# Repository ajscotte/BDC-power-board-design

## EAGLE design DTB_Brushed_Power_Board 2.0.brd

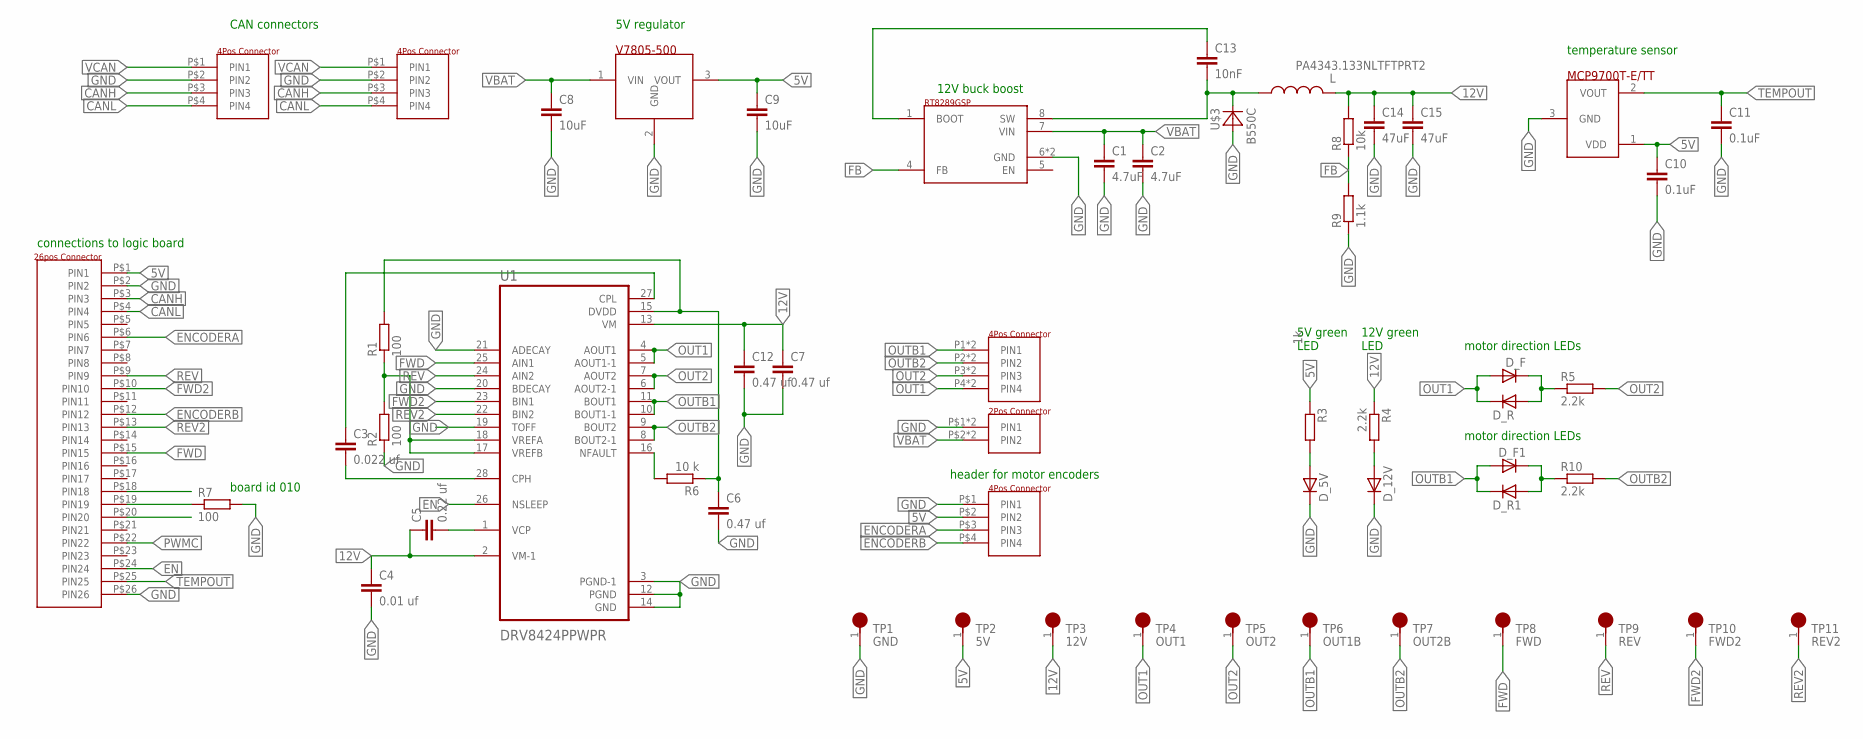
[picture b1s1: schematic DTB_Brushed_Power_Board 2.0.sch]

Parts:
C1, C2: 4.7uF; C1206
C3: 0.022 uf; C1206
C4: 0.01 uf; C1206
C5: 0.22 uf; C1206
C6, C7, C12: 0.47 uf; C1206
C8, C9: 10uF; C1206
C10, C11: 0.1uF; C0603
C13: 10nF; C1206
C14, C15: 47uF; C1206
D_5V, D_12V: LED0603; DO0603
D_F, D_F1: LED0603; DO0603
D_R, D_R1: LED0603; DO0603
L: PA4343.133NLTFTPRT2; INDM140128X650N
R1, R2, R7: 100; R0603
R3: 1k; R0603
R4, R5, R10: 2.2k; R0603
R6: 10 k; R0603
R8: 10k; R0603
R9: 1.1k; R0603
TP1: GND; HARWIN_S2751-46R
TP2: 5V; HARWIN_S2751-46R
TP3: 12V; HARWIN_S2751-46R
TP4: OUT1; HARWIN_S2751-46R
TP5: OUT2; HARWIN_S2751-46R
TP6: OUT1B; HARWIN_S2751-46R
TP7: OUT2B; HARWIN_S2751-46R
TP8: FWD; HARWIN_S2751-46R
TP9: REV; HARWIN_S2751-46R
TP10: FWD2; HARWIN_S2751-46R
TP11: REV2; HARWIN_S2751-46R
U1: DRV8424PPWPR; IC_TPS61196PWPRQ1
U$2: RT8289GSP; SO8
U$3: B550C; SMC
U$4: 2POS_CONNECTOR,1X2_45A_POWERPOLE; POWERPOLE_45A_1X2
U$6: 4POS_CONNECTORPOWERPOLE_1X4; POWERPOLE_45A_1X4
U$7, U$8: 4POS_CONNECTORMOLEX_MICROFIT3.0_RA_4PIN_2ROW; MOLEX_MICROFIT3.0_0430450400
U$9: V7805-500; SIP3
U$10: 26POS_CONNECTORN2526-6002-RB; N2526-6002-RB
U$11: MCP9700T-E/TT; SOT23
U$12: 4POS_CONNECTOR.1"HEADER; 4POS_HEADER_.1"

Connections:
5V: C9.1, C10.1, R3.1, TP2.1, U$9.3 (VOUT), U$10.P$1 (PIN1), U$11.1 (VDD), U$12.P$2 (PIN2)
12V: C4.1, C5.1, C7.1, C12.1, C14.1, C15.1, L.2, R4.1, R8.2, TP3.1, U1.2 (VM-1), U1.13 (VM)
BOOT: C13.1, U$2.1 (BOOT)
CANH: U$7.P$3 (PIN3), U$8.P$3 (PIN3), U$10.P$3 (PIN3)
CANL: U$7.P$4 (PIN4), U$8.P$4 (PIN4), U$10.P$4 (PIN4)
EN: U1.26 (NSLEEP), U$10.P$24 (PIN24)
ENCODERA: U$10.P$6 (PIN6), U$12.P$3 (PIN3)
ENCODERB: U$10.P$12 (PIN12), U$12.P$4 (PIN4)
FB: R8.1, R9.2, U$2.4 (FB)
FWD: TP8.1, U1.25 (AIN1), U$10.P$15 (PIN15)
FWD2: TP10.1, U1.23 (BIN1), U$10.P$10 (PIN10)
GND: C1.2, C2.2, C4.2, C6.2, C7.2, C8.2, C9.2, C10.2, C11.2, C12.2, C14.2, C15.2, D_5V.2 (C), D_12V.2 (C), R2.1, R7.2, R9.1, TP1.1, U1.3 (PGND-1), U1.12 (PGND), U1.14 (GND), U1.19 (TOFF), U1.20 (BDECAY), U1.21 (ADECAY), U$2.6 (GND), U$2.GND,EXPOSEDPAD (GND), U$3.A, U$4.P$1 (PIN1), U$4.P$5 (PIN1), U$7.P$2 (PIN2), U$8.P$2 (PIN2), U$9.2 (GND), U$10.P$2 (PIN2), U$10.P$26 (PIN26), U$11.3 (GND), U$12.P$1 (PIN1)
unnamed: R6.2, U1.16 (NFAULT)
unnamed: D_F.2 (C), D_R.1 (A), R5.1
unnamed: R7.1, U$10.P$19 (PIN19)
unnamed: C6.1, R1.2, R6.1, U1.15 (DVDD)
unnamed: D_5V.1 (A), R3.2
unnamed: D_12V.1 (A), R4.2
unnamed: C5.2, U1.1 (VCP)
unnamed: C13.2, L.1, U$2.8 (SW), U$3.C
unnamed: D_F1.2 (C), D_R1.1 (A), R10.1
unnamed: R1.1, R2.2, U1.17 (VREFB), U1.18 (VREFA)
unnamed: C3.2, U1.28 (CPH)
OUT1: D_F.1 (A), D_R.2 (C), TP4.1, U1.4 (AOUT1), U1.5 (AOUT1-1), U$6.P4 (PIN4), U$6.P4B (PIN4)
OUT2: R5.2, TP5.1, U1.6 (AOUT2-1), U1.7 (AOUT2), U$6.P3 (PIN3), U$6.P3B (PIN3)
OUTB1: D_F1.1 (A), D_R1.2 (C), TP6.1, U1.10 (BOUT1-1), U1.11 (BOUT1), U$6.P1 (PIN1), U$6.P1B (PIN1)
OUTB2: R10.2, TP7.1, U1.8 (BOUT2-1), U1.9 (BOUT2), U$6.P2 (PIN2), U$6.P2B (PIN2)
PWMC: U$10.P$22 (PIN22)
REV: TP9.1, U1.24 (AIN2), U$10.P$9 (PIN9)
REV2: TP11.1, U1.22 (BIN2), U$10.P$13 (PIN13)
TEMPOUT: C11.1, U$10.P$25 (PIN25), U$11.2 (VOUT)
VBAT: C1.1, C2.1, C8.1, U$2.7 (VIN), U$4.P$2 (PIN2), U$4.P$6 (PIN2), U$9.1 (VIN)
VBAT1: C3.1, U1.27 (CPL)
VCAN: U$7.P$1 (PIN1), U$8.P$1 (PIN1)

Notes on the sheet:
CAN connectors
5V regulator
connections to logic board
temperature sensor
board id 010
5V green LED
12V green LED
motor direction LEDs
header for motor encoders
12V buck boost

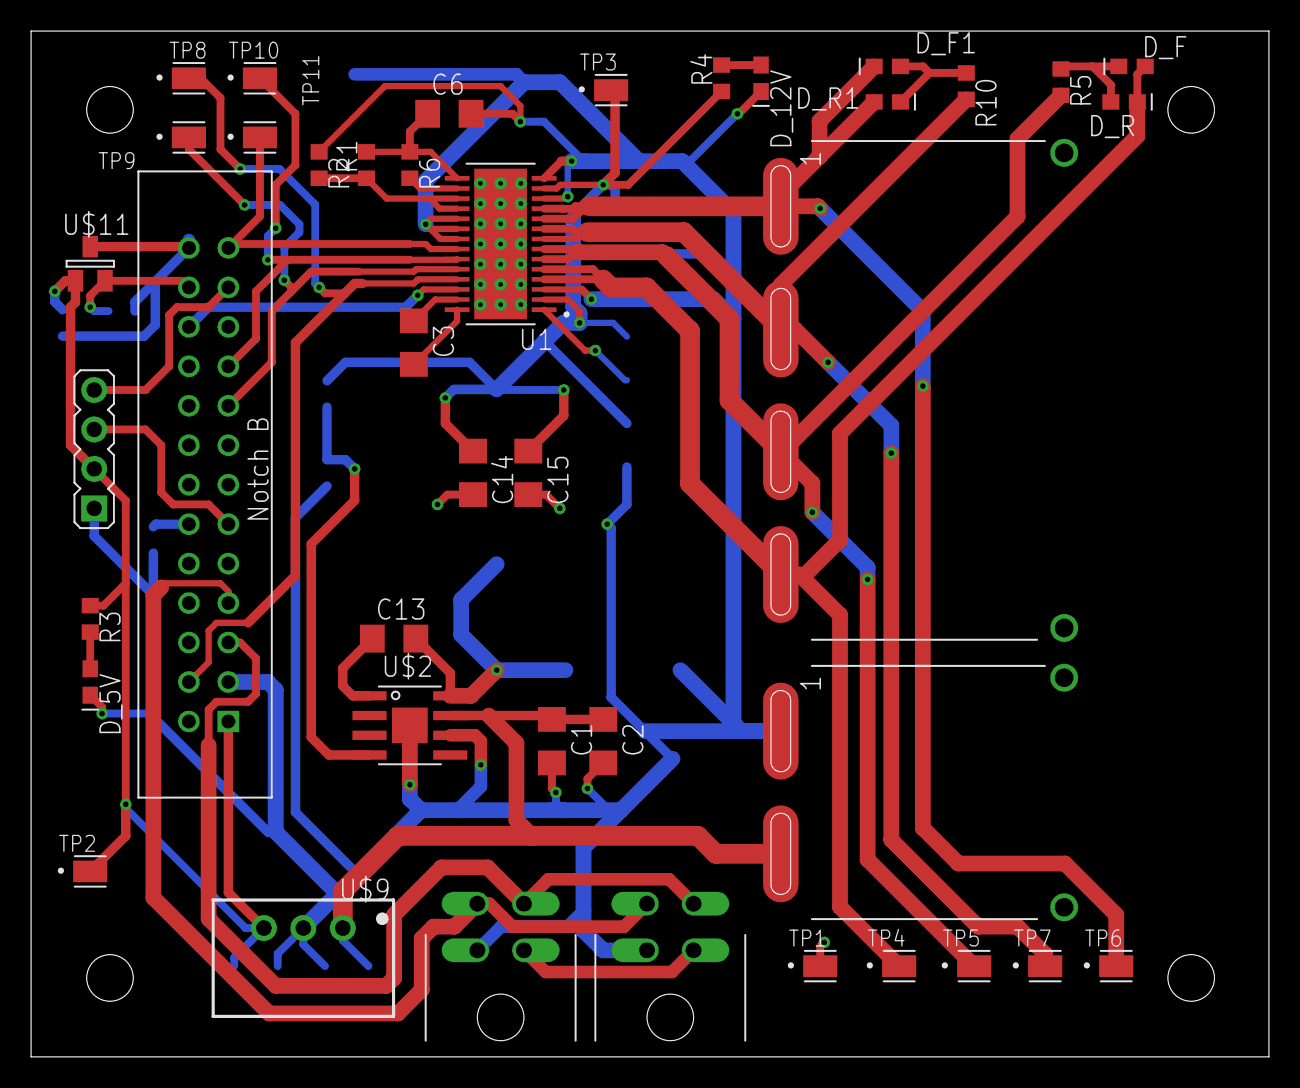
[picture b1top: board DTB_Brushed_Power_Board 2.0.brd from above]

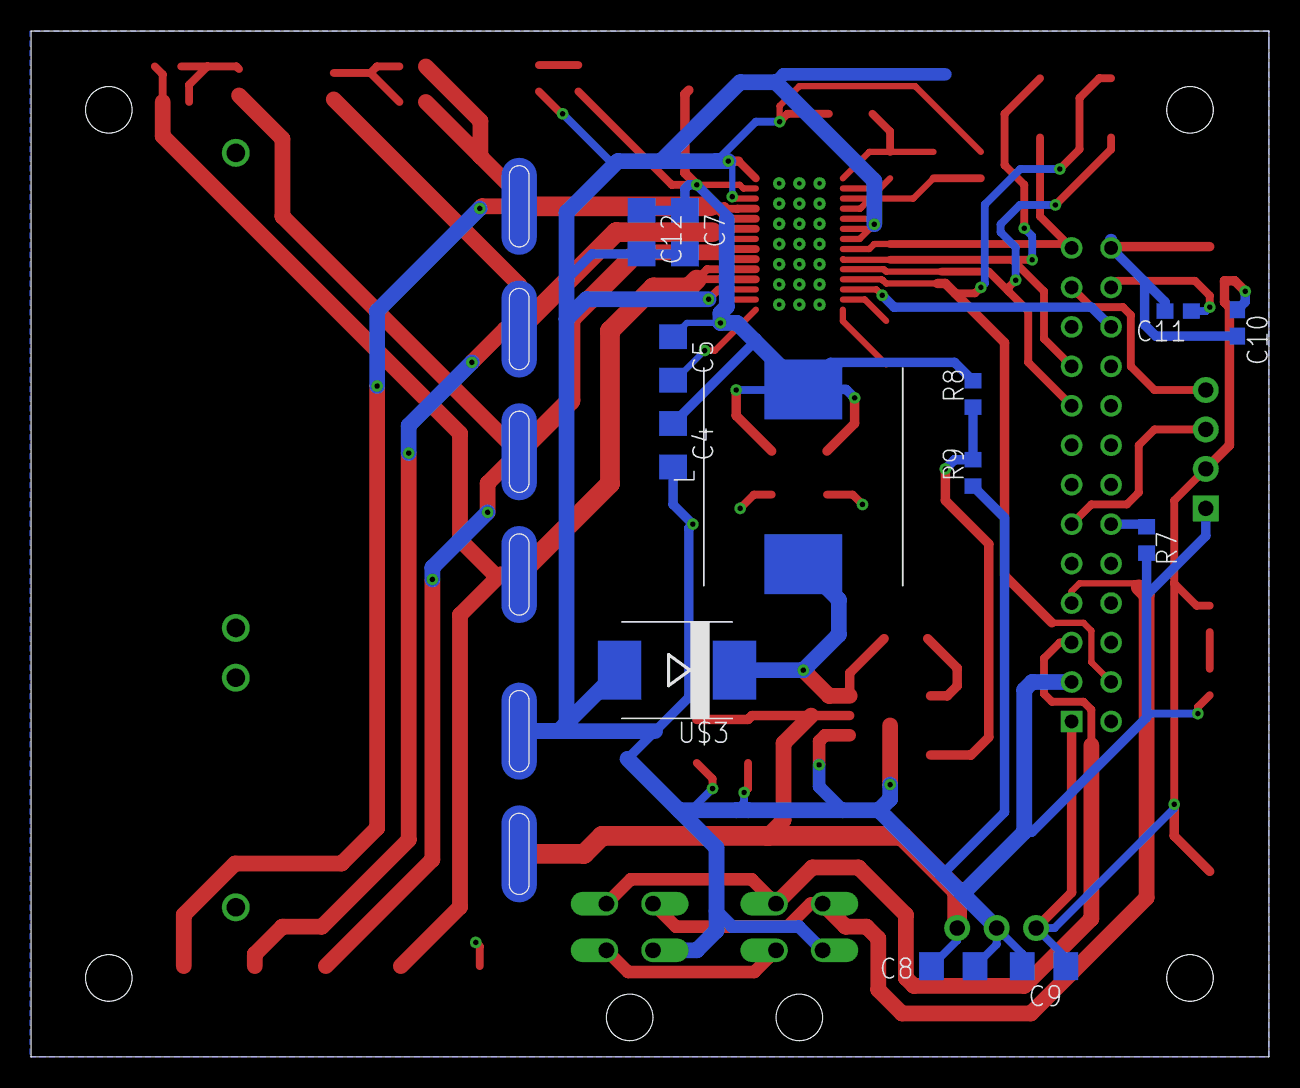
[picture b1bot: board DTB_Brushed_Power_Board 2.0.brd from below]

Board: 2 copper layers, 79.7 x 66.0 mm, 54 parts (13 on the bottom side), 33 nets.

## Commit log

2022-03-07 board upload
